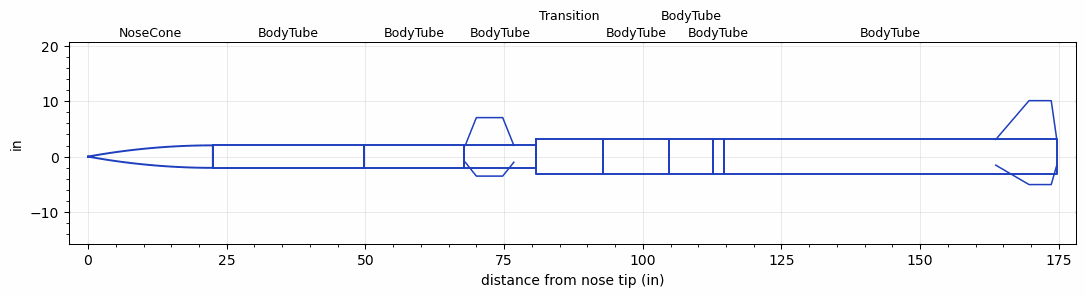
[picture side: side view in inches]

<RASAeroDocument>
 <FileVersion>2</FileVersion>
 <RocketDesign>
  <NoseCone>
   <Length>22.5</Length>
   <Diameter>4.055</Diameter>
   <Shape>Tangent Ogive</Shape>
   <Location>0</Location>
  </NoseCone>
  <BodyTube>
   <Length>27.25</Length>
   <Diameter>4.055</Diameter>
   <Location>22.5</Location>
  </BodyTube>
  <BodyTube>
   <Length>18</Length>
   <Diameter>4.055</Diameter>
   <Location>49.75</Location>
  </BodyTube>
  <BodyTube>
   <Length>13</Length>
   <Diameter>4.055</Diameter>
   <Location>67.75</Location>
   <Fin>
    <Count>3</Count>
    <Chord>8.75</Chord>
    <Span>5</Span>
    <SweepDistance>2</SweepDistance>
    <TipChord>4.75</TipChord>
    <Thickness>0.125</Thickness>
    <Location>12.75</Location>
    <AirfoilSection>Rounded</AirfoilSection>
   </Fin>
  </BodyTube>
  <Transition>
   <Length>12</Length>
   <Diameter>6.17</Diameter>
   <Location>80.75</Location>
   <RearDiameter>6.17</RearDiameter>
  </Transition>
  <BodyTube>
   <Length>12</Length>
   <Diameter>6.17</Diameter>
   <Location>92.75</Location>
  </BodyTube>
  <BodyTube>
   <Length>7.874</Length>
   <Diameter>6.17</Diameter>
   <Location>104.75</Location>
  </BodyTube>
  <BodyTube>
   <Length>2</Length>
   <Diameter>6.17</Diameter>
   <Location>112.624</Location>
  </BodyTube>
  <BodyTube>
   <Length>60</Length>
   <Diameter>6.17</Diameter>
   <Location>114.624</Location>
   <Fin>
    <Count>3</Count>
    <Chord>11</Chord>
    <Span>7</Span>
    <SweepDistance>6</SweepDistance>
    <TipChord>4</TipChord>
    <Thickness>0.125</Thickness>
    <Location>11</Location>
    <AirfoilSection>Rounded</AirfoilSection>
   </Fin>
  </BodyTube>
  <Surface>Smooth (Zero Roughness)</Surface>
  <ModifiedBarrowman>False</ModifiedBarrowman>
  <Turbulence>False</Turbulence>
  <UseBooster1>False</UseBooster1>
  <UseBooster2>False</UseBooster2>
 </RocketDesign>
 <LaunchSite>
  <Altitude>0</Altitude>
  <Pressure>0</Pressure>
  <RodAngle>0</RodAngle>
  <RodLength>4</RodLength>
  <Temperature>74</Temperature>
  <WindSpeed>0</WindSpeed>
 </LaunchSite>
 <Recovery>
  <Altitude1>1000</Altitude1>
  <Altitude2>1000</Altitude2>
  <DeviceType1>None</DeviceType1>
  <DeviceType2>None</DeviceType2>
  <Event1>False</Event1>
  <Event2>False</Event2>
  <Size1>1</Size1>
  <Size2>1</Size2>
  <EventType1>None</EventType1>
  <EventType2>None</EventType2>
  <CD1>1.33</CD1>
  <CD2>1.33</CD2>
 </Recovery>
 <SimulationList>
  <Simulation>
   <SustainerEngine>K735-SK-P  (CTI)</SustainerEngine>
   <SustainerLaunchWt>0</SustainerLaunchWt>
   <SustainerCG>0</SustainerCG>
   <SustainerIgnitionDelay>0</SustainerIgnitionDelay>
   <Booster1Engine>N2540-GR-P  (CTI)</Booster1Engine>
   <Booster1LaunchWt>49260</Booster1LaunchWt>
   <Booster1SeparationDelay>0</Booster1SeparationDelay>
   <Booster1IgnitionDelay>0</Booster1IgnitionDelay>
   <Booster1CG>116</Booster1CG>
   <IncludeBooster1>True</IncludeBooster1>
   <Booster2Delay>0</Booster2Delay>
   <IncludeBooster2>False</IncludeBooster2>
  </Simulation>
 </SimulationList>
</RASAeroDocument>
